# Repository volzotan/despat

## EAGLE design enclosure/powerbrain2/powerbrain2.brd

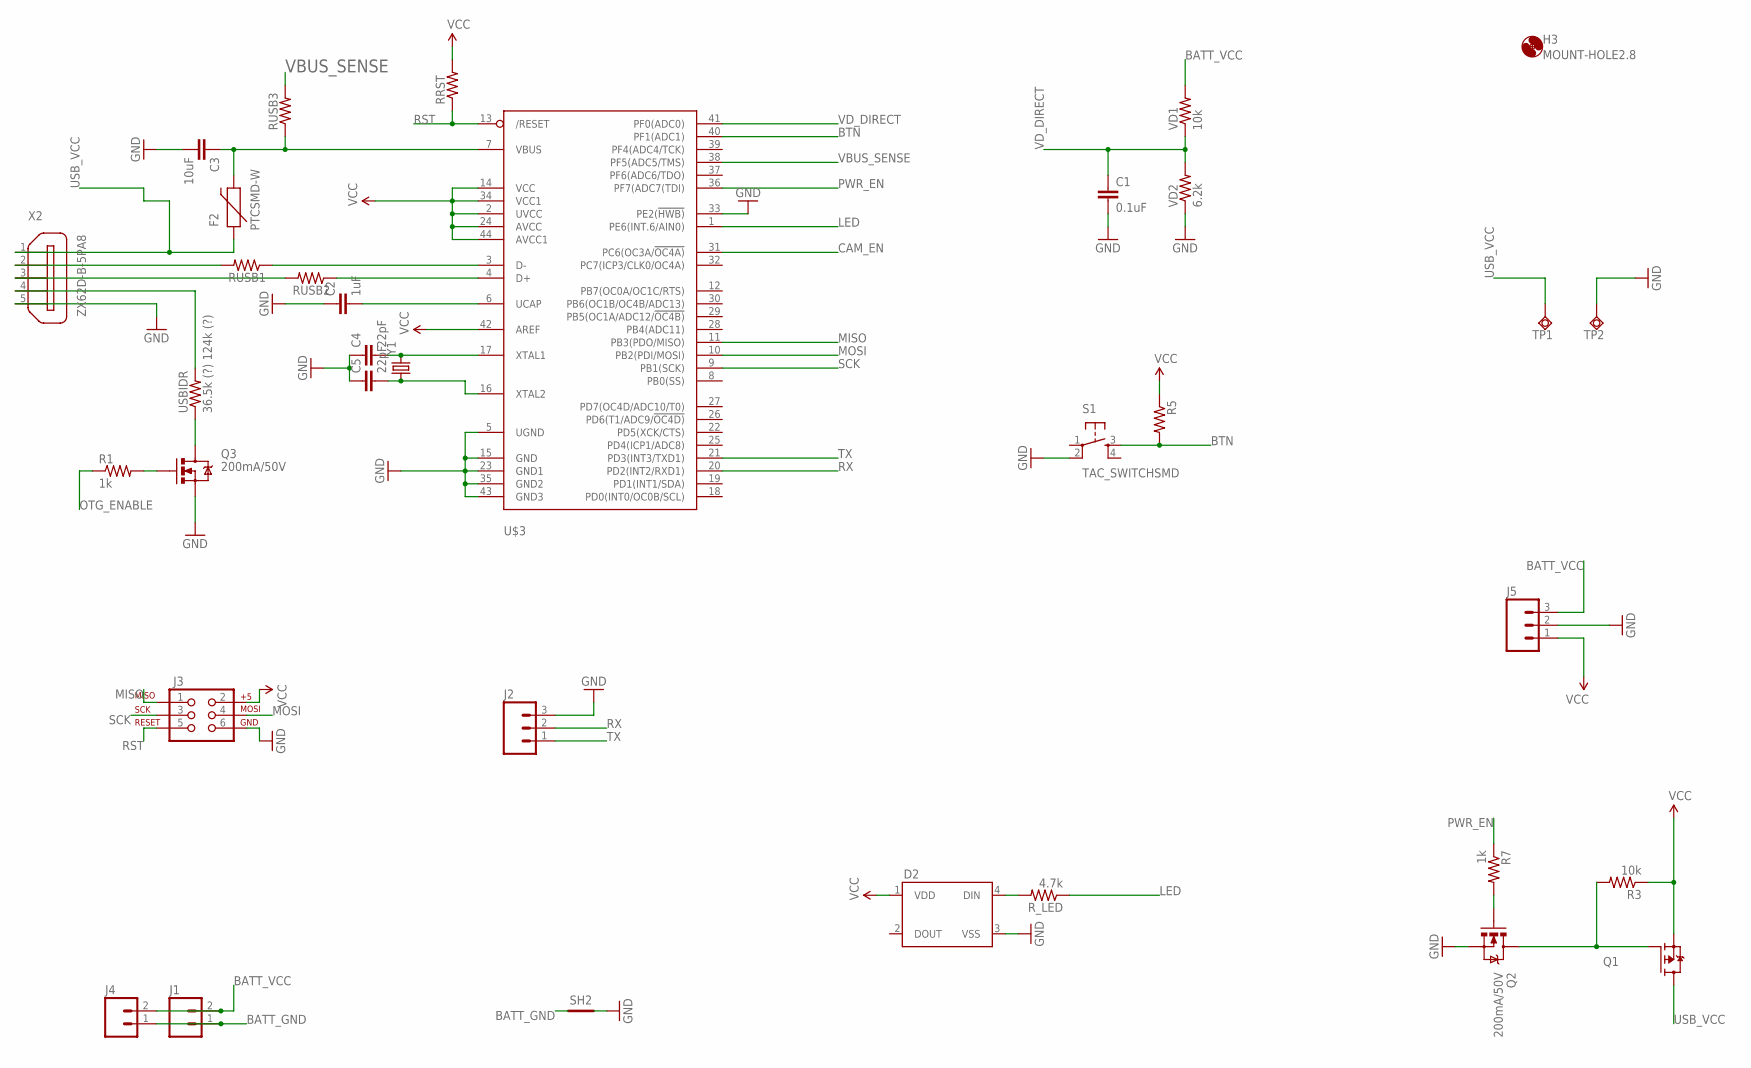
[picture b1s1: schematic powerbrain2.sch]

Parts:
C1: 0.1uF; 1206
C2: 1uF; 1206
C3: 10uF; 1206
C4, C5: 22pF; 1206
D2: WS2812B
F2: PTCSMD-W; PTC-1206-WIDE
H3: MOUNT-HOLE2.8; 2,8
J1, J4: M02LOCK; 1X02_LOCK
J2: M03PTH; 1X03
J3: AVR_SPI_PRG_6PTH; 2X3
J5: M03LOCK; 1X03_LOCK
Q1: FDD4141TO252; TO252
Q2, Q3: 200mA/50V; SOT23-3
R1, R7: 1k; 1206
R3: 10k; 1206
R5: RESISTOR1206; 1206
RRST: RESISTOR1206; 1206
RUSB1, RUSB2, RUSB3: RESISTOR1206; 1206
R_LED: 4.7k; 1206
S1: TAC_SWITCHSMD; TACTILE-PTH
SH2: SHORT-HT5; SHORT_TOP-50
TP1, TP2: TPSQTP20R; TP20R
U$3: ATMEGA32U4-AU; TQFP44
USBIDR: 36.5k (?) 124k (?); 1206
VD1: 10k; 1206
VD2: 6.2k; 1206
X2: ZX62D-B-5PA8
Y1: CRYSTALCRYSTAL-SMD-5X3-16MHZ; CRYSTAL-SMD-5X3

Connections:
$N23: C3.1, F2.2, RUSB3.1, U$3.7 (VBUS)
BATT_GND: J1.1, J4.1, SH2.1
BATT_VCC: J1.2, J4.2, J5.3, VD1.2
BTN: R5.2, S1.3, U$3.40 (PF1(ADC1))
CAM_EN: U$3.31 (PC6(OC3A/!OC4A))
GND: C1.2, C2.1, C3.2, C4.1, C5.1, D2.3 (VSS), J2.3, J3.6, J5.2, Q2.2 (S), Q3.2 (S), S1.2, SH2.2, TP2.TP, U$3.5 (UGND), U$3.15 (GND), U$3.23 (GND1), U$3.33 (PE2(!HWB)), U$3.35 (GND2), U$3.43 (GND3), VD2.1, X2.5
LED: R_LED.1, U$3.1 (PE6(INT.6/AIN0))
MISO: J3.1, U$3.11 (PB3(PDO/MISO))
MOSI: J3.4, U$3.10 (PB2(PDI/MOSI))
unnamed: USBIDR.2, X2.4
unnamed: Q3.3 (D), USBIDR.1
unnamed: Q3.1 (G), R1.2
unnamed: RUSB1.1, U$3.3 (D-)
unnamed: RUSB2.1, U$3.4 (D+)
unnamed: Q1.1 (G), Q2.3 (D), R3.2
unnamed: D2.4 (DIN), R_LED.2
unnamed: C4.2, U$3.17 (XTAL1), Y1.3 (2)
unnamed: C5.2, U$3.16 (XTAL2), Y1.1
unnamed: RUSB1.2, X2.2
unnamed: RUSB2.2, X2.3
unnamed: Q2.1 (G), R7.2
unnamed: C2.2, U$3.6 (UCAP)
OTG_ENABLE: R1.1
PWR_EN: R7.1, U$3.36 (PF7(ADC7(TDI))
RST: J3.5, RRST.1, U$3.13 (/RESET)
RX: J2.2, U$3.20 (PD2(INT2/RXD1))
SCK: J3.3, U$3.9 (PB1(SCK))
TX: J2.1, U$3.21 (PD3(INT3/TXD1))
USB_VCC: F2.1, Q1.3 (D), TP1.TP, X2.1
VBUS_SENSE: RUSB3.2, U$3.38 (PF5(ADC5/TMS))
VCC: D2.1 (VDD), J3.2, J5.1, Q1.2 (S), R3.1, R5.1, RRST.2, U$3.2 (UVCC), U$3.14 (VCC), U$3.24 (AVCC), U$3.34 (VCC1), U$3.42 (AREF), U$3.44 (AVCC1)
VD_DIRECT: C1.1, U$3.41 (PF0(ADC0)), VD1.1, VD2.2

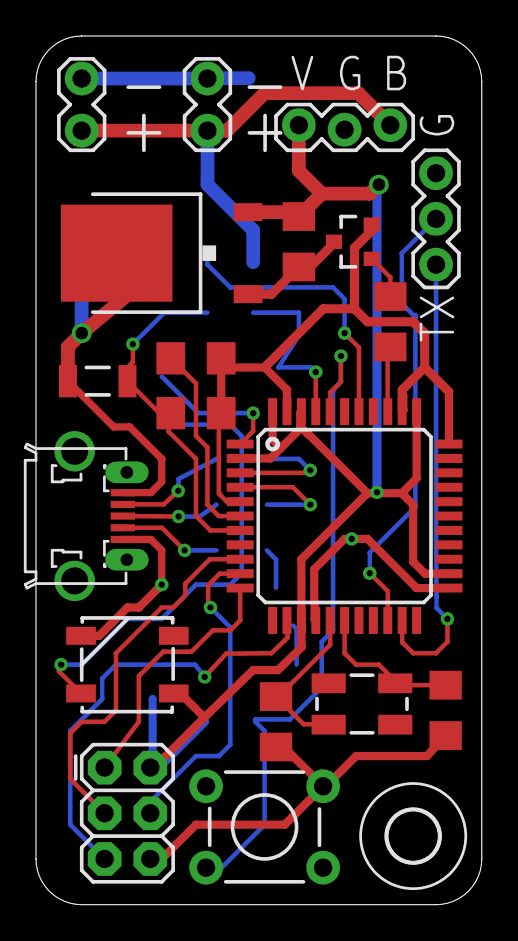
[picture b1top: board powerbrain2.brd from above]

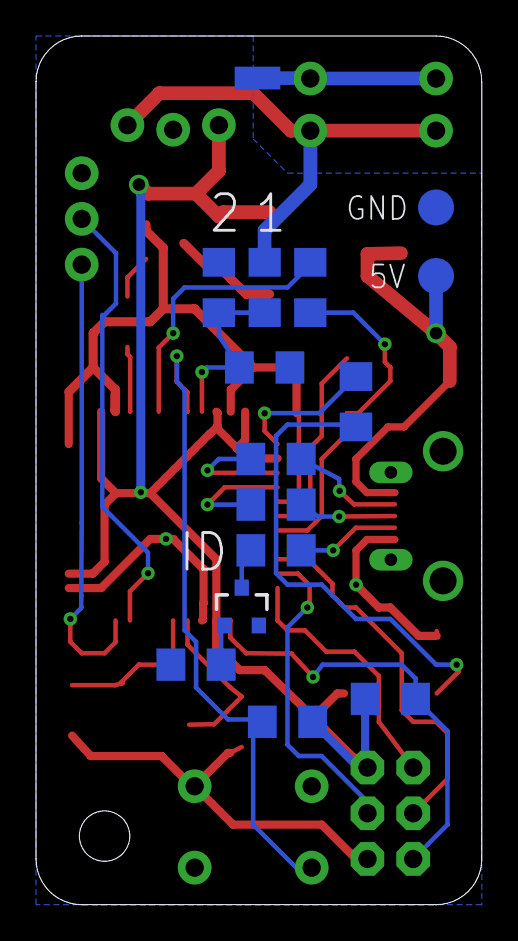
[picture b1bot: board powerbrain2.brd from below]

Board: 2 copper layers, 24.8 x 48.3 mm, 35 parts (15 on the bottom side), 30 nets.

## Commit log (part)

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2017-11-09 Services are checking for internet connection now
2017-11-15 powerbrain2 sent to fab
2017-12-29 removed CameraController1 burst mode added
2018-01-02 removed CameraAdapter Interface
2018-01-04 CameraController2 overhaul: taking images without preview
2018-01-05 cameraController2 overhaul: bugfixes
2018-01-06 CameraController2 renamed
2018-01-08 CameraController: bugfixes ShutterService: WakeLock added (apparently) BufferQueue abandoned fixed
2018-01-10 camera-close-while-sleeping bug workaround
2018-01-10 enclosure: refactoring and socket_flat added
2018-01-11 CameraController: added delay
2018-01-12 enclosure: bugfix top hinge height
2018-01-12 CameraController ControllerCallback used
2018-01-13 CameraController callback cleaned up
2018-01-15 enclosure: 3d printed flex seal
2018-01-16 enclosure: new latch mechanism
2018-01-16 enclosure: new clamp
2018-01-17 bugfix: camera handling
2018-01-17 added option to disable ImageRoll deletions
2018-01-17 Enclosure: removed semiflex seal
2018-01-17 RoomDatabase extended
2018-01-18 further integration of the room library
2018-01-19 RecordingSession: imagesTaken
2018-01-20 added event table
2018-01-20 minor changes Room refactoring
2018-01-21 toggleCamera: half bugfix
2018-01-21 reboot on critical error logcat backup
2018-01-21 Nexus5 camera-close-bug
2018-01-22 colorful animal session naming scheme
2018-01-23 servpat: hardcoded show graph of last 3 days
2018-01-26 script to fetch database from android device
2018-01-26 Room refactoring (sid = id) sync adapter
2018-01-29 Sync Adapter status & event code
2018-01-29 servpat sync changes (status&event)
2018-01-29 servpat templates bugfixes
2018-01-30 sync adapter: Heartbeat Service triggers manual sync
2018-01-30 CameraController: BackgroundHandler = null
2018-01-30 despat: minor changes
2018-01-31 timebox style fields in session
2018-02-01 either redirect or backup logcat
2018-02-01 ShutterService overhaul: runs now as a permanent foreground service
2018-02-04 ShutterService: Notification handling cleaned up
2018-02-04 servpat: capture syncing
2018-02-05 added wakelock events
2018-02-06 minor cleanup
2018-02-06 testprint: ridge height increased
2018-02-06 CameraController1: burst bugfix ZTE Axon picture size bugfix
2018-02-07 nginx conf bugfix (now /upload doesn't reply 413 on files bigger than 1.5MB)
2018-02-08 enclosure: bugfixes sizeTop/sizeBot
2018-02-09 Sync by ShutterService with Knock-command
2018-02-09 fixed ISO value option
2018-02-12 CameraController1: restart camera on startPreview exception
2018-02-12 CameraController3
2018-02-13 bugfix syncing sessions
2018-02-14 Sync bugfixes
2018-02-14 RoomDatabase JSON file
2018-02-17 CameraController2: 3A modes and printing CameraCharacteristics
2018-02-17 CameraController2: added CameraCharacteristics info for non legacy devices
2018-02-17 minor changes and bugfixes
2018-02-18 ImageRollover & CameraController2: partial RAW support
2018-02-18 CameraController2: ImageSaver instead of CaptureMetadata
2018-02-19 enclosure: changed round to straight corners
2018-02-20 ui cleanups
2018-02-20 reformatted Config
2018-02-23 Sync: max 900 elements per Sync (lazy solution for maxSize of 999 SQL arguments per query)
2018-03-02 eventlogging for display on/off while ShutterService is active bugfix minSyncInterval
2018-03-05 bugfix imageSaver instance handling
2018-03-08 Orchestrator: resume after reboot bugfix room date conversion minor cleanups
2018-03-09 new notification style minor cleanups
2018-03-10 bugfixes
2018-03-11 enclosure: hinge z-offset, wedge tolerances, seal cutout
2018-03-13 bugfix ImageRollover freeSpace calculation
2018-03-16 enclosure: wedge semiflex, MotoZ cavity
2018-03-19 enclosure: minor tolerance tweaks and hex support for flat top
2018-03-23 detection test scripts
2018-03-24 detection: tile_generator cleanup
2018-03-26 incomplete changes for persistent camera
2018-03-29 persistent camera for camera controller 1
2018-03-29 enclosure: support for heat inserts instead of standard nyloc nuts
2018-04-02 enclosure: bugfix hinge placement
2018-04-03 persistent camera update: background tasks
2018-04-03 shutterService process gets own name
2018-04-03 First stub of TensorflowLite integration
2018-04-04 TensorflowMobile instead of TensorflowLite
2018-04-07 better way of using the built-in settings/preferences mechanism
2018-04-10 test script for opencvs MOG background subtraction
2018-04-11 inference test bugfixes
2018-04-13 preferences not managed in xml files anymore
2018-04-14 preferences and config transition finally functionally
2018-04-15 enclosure: phone dependent models moved to own files
2018-04-15 enclosure: bugfixes for new phone files
2018-04-15 enclosure: bugfix tripod hole size
2018-04-15 TensorflowLite Playground added
2018-04-16 ShutterService: minor changes for persistentCamera
2018-04-16 stubs for new classes
2018-04-18 ShutterService: bugfixes for non persistent camera
2018-04-18 enclosure: wedge for socket nut
2018-04-19 DefaultExceptionHandlers for Threads, persistent errors in DB
2018-04-20 ShutterService: further improvements in error handling
2018-04-23 despat: drawing of bounding boxes
2018-04-25 inference_test.py can now generate PascalVOC xml annotation files tilemanager support now non square tiles
2018-04-25 ShutterService: bugfix for clean camera restarts
2018-04-25 annotations: conversion for json to PascalVoc xml
2018-04-27 RecordingSession schedule glitch test
2018-04-27 refactoring detector interface
2018-04-28 evaluation for precision and recall
2018-04-29 evaluate: draw precision recall curve
2018-05-01 refactoring several python scripts heatmap plots
2018-05-02 matplotlib for OSM tiles
2018-05-05 postprocessing scripts
2018-05-08 postprocessing: minor changes
2018-05-09 visualization: csv file contains now more info than just latlon
2018-05-13 visualization: canvas embedded in SVG
2018-05-13 visualization: mapprovider selection menu
2018-05-15 visualization: added column names to CSV file loading screen
2018-05-16 visualization: refactoring and timebar
2018-05-19 visualization: non zoom variant
2018-05-20 visualization: solution for hexmap panning and zooming
2018-05-21 visualization: layer hexmap legend
2018-05-23 visualization: filtering with brushes and proper timeline axis
2018-05-23 visualization: filtering with brushes and proper timeline axis, part 2
2018-05-28 added google maps activity
2018-05-28 removed old SettingsActivity
2018-05-28 removed unused files
2018-05-29 Session User Interface is now based on fragments moving classes to new userinterface package
2018-05-30 compressor added saveguards for memory overconsumption
2018-05-30 compressor matrix serialization
2018-06-02 bugfix: no integer parameters for setText()
2018-06-02 DevicePositioner and Proximity Sensor
2018-06-04 Share files via Share Intent
2018-06-04 Toolbar and HomographyPointFragment added
2018-06-05 Homography point listing
2018-06-05 ShutterService reduced notification priority
2018-06-06 restructured the whole session list again
2018-06-06 db: cascading deletes
2018-06-06 SessionList: swipe to delete
2018-06-08 new mainactivity layout and icons
2018-06-08 APK upload script
2018-06-09 MainActivity UI overhaul UI bugfixes
2018-06-09 minor changes new activities point and intro
2018-06-09 Sysinfo box
2018-06-10 refactoring
2018-06-10 HomographyCalculator
2018-06-13 PointActivity cleanup in Detector display functions
2018-06-13 refactoring / cleaning
2018-06-15 HomographyMatrix serialization for db Sync upload battery temperature
2018-06-15 room db schema from last commit
2018-06-15 servpat: temperature graph
2018-06-15 docpage: created guide articles
2018-06-15 removed IDE generated author comments
2018-06-15 added Locale to String.format
2018-06-16 Progressbar notification for recognitionservice
2018-06-17 CameraConfig added
2018-06-17 bugfix android Oreo notification channel sounds
2018-06-20 new icon
2018-06-21 bugfixes: drawSurface and devicePositioner
2018-06-21 deviceInfo at startup
2018-06-25 bugfix
2018-06-27 minor changes pixel size plot now supports multiple input directories
2018-07-03 updated evaluation scripts
2018-07-03 docpage stubs
2018-07-04 zoom enhancements, deviceInfo enhancements
2018-07-12 DevicePositioner bugfix Gyro data is no longer used for device positioning
2018-07-12 bugfix devicePositioner (only landscape)
2018-07-12 bugfix: Preference summaries are not updated in SettingsActivity
2018-07-18 CameraConfig handling
2018-07-23 vizpat: multi camera and multi class support
2018-07-23 evaluation: mAP requires max interpolated precision
2018-07-26 10fold speed-up for tilemanager by dropping PIL evaluation script improvements
2018-08-01 evaluation script changes
2018-08-10 Heartbeat manual trigger
2018-08-10 cleaned up the powerbrain2 schematics
2018-08-17 bugfixes visualization (scattermap always present on chrome) minor changes
2018-08-18 GPL3 license
2018-08-18 removed DespatPlayground
2018-08-23 docpage updates
2018-08-23 cleaning up visualization
2018-08-23 Set theme jekyll-theme-minimal
2018-08-25 viz: refactoring
2018-08-31 qa.py
2018-09-06 github pages docs changes in jekylls config
2018-09-06 docs: urlsurlsurls
2018-09-11 jitter for tilemanager
2018-09-16 action detection for the visualization tool
2018-09-25 Benchmark now in Database Session contains additional information about session specific settings fidelity setting
2018-09-25 sysinfobox minimal improvements
2018-09-28 Refactoring of RecordingSession to SessionManager Additional Config objects
2018-09-29 Storing CameraConfig now in db
2018-10-03 Compressor working now in increments
2018-10-06 cleanup burst images reduced to 1 session exporting extended
2018-10-09 replaced PNG icons by SVG vector assets
2018-10-10 bugfix Configure CameraConfig
2018-10-13 Bugfixes SessionListActivity
2018-10-13 minor UI improvements
2018-10-16 androidx migration
2018-10-16 bugfixes and Room schema updates
2018-10-18 fixed button appearances
2018-10-22 bugfixes XML resources
2018-10-22 Permission requesting in Tour
2018-10-23 Example Session Data first part
2018-10-23 progress in docs
2018-10-26 Example Dataset
2018-10-27 draw compressed image box overlay in the background
2018-10-27 Exposure Compensation added to CameraController2
2018-10-27 Snackbar on MainActivity centered bugfixes Tour
2018-10-27 minor and incomplete changes
2018-10-27 gitignore updated
2018-10-29 Powerbrain deleted
2018-10-29 cleaned up dependencies Benchmark improved
2018-10-30 Computation time estimation improved
2018-11-05 bugfix HomographyPoint deletion
2018-11-12 icon update
2018-11-12 Removed Mid Fidelity network to reduce APK size
2018-11-16 load CNN models from OBB
2018-11-17 Google Play Store License Library
2018-11-21 Google Downloader Library updated License Library
2018-11-24 refactor SettingsActivity
2018-11-25 Extended Settings pane
2018-11-25 CaptureInfo object to save capture information about single captures
2018-11-25 CompressorService enable settings
2018-12-01 enclosure: LG G6 phone model
2018-12-02 enclosure: bugfix LG G6 wide angle camera vignette
2018-12-02 exposure value threshold setting
2019-01-23 misc
2019-01-24 grade plugin update
2019-02-20 vizpat: loading of local ZIP archives
2019-02-23 new docs
2019-02-23 moved docs4 to docs
2019-02-24 bugfix image folder handling
2019-04-17 docs updated
2019-04-17 List of all events added to Session Tabs
2019-04-18 gradle and dependencies update
2019-04-18 InfoFragment: more graphs
2019-05-14 OBB loading improved
2019-05-14 version number bump minor changes
2019-07-02 updated googleplaylicenselibrary
2019-07-02 Syncing of exposureValues added and regular image upload reenabled
2019-07-11 syncing free memory sizes
2019-07-11 AlarmManager ELAPSED_REALTIME instead of RTC bugfixes
2019-07-15 API level 28 compatibility
2019-07-30 backup alarm, bugfixes and memory leak changes
2019-07-30 added DeviceLocationService
2019-10-12 gradle version bump
2019-11-04 transfer learning: export of ground truth tiles
2019-11-05 transfer learning: export tfrecord

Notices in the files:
parts and their libraries:
SparkFun-Connectors: Licensing: Creative Commons ShareAlike 4.0 International - https://creativecommons.org/licenses/by-sa/4.0
